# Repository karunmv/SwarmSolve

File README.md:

### Main
Entrypoint.

### esp_now_comms
Functions for inter-robot communications.

### feature_detection
Detects the current features of the maze.

Provides an interface to maneuver these features.

### motor_control
Drives the motors.

### QTRX-MD-NRC
Provides an interface for reading IR sensor values.

### utils
Utilitiy functions.

# TODO

Figure out watchdog thing

Convert num pulses to distance
Have exploration strategy be decided at runtime by which button gets pressed
Basic collision avoidance
generalize exploration algorithm

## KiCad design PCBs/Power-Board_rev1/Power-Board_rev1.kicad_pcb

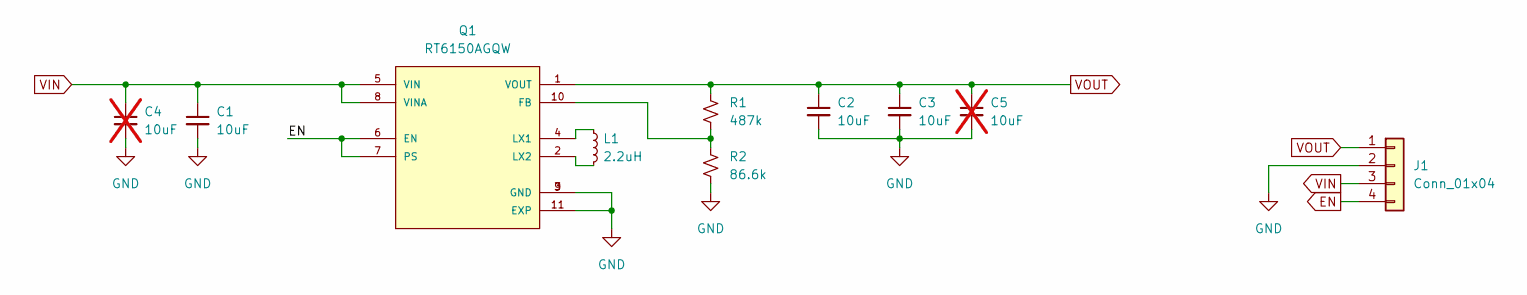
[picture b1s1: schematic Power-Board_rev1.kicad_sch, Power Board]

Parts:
C1, C2, C3: 10uF; C_0805_2012Metric_Pad1.18x1.45mm_HandSolder; JLCPCB Part# C95841
C4, C5: 10uF; C_0805_2012Metric_Pad1.18x1.45mm_HandSolder; JLCPCB Part# C95841; not fitted
J1: Conn_01x04; PinHeader_1x04_P2.54mm_Vertical_GND2
L1: 2.2uH; L_Changjiang_FTC252012S; JLCPCB Part# C5832372
Q1: RT6150AGQW; SON50P300X300X80-11N; JLCPCB Part# C147971
R1: 487k; R_0603_1608Metric_Pad0.98x0.95mm_HandSolder; JLCPCB Part# C23183
R2: 86.6k; R_0603_1608Metric_Pad0.98x0.95mm_HandSolder; JLCPCB Part# C23121

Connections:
/EN: J1.4, Q1.6 (EN), Q1.7 (PS)
/VIN: C1.1, C4.1, J1.3, Q1.5 (VIN), Q1.8 (VINA)
/VOUT: C2.1, C3.1, C5.1, J1.1, Q1.1 (VOUT), R1.1
GND: C1.2, C2.2, C3.2, C4.2, C5.2, J1.2, Q1.3 (GND), Q1.9 (GND), Q1.11 (EXP), R2.2
unnamed: Q1.10 (FB), R1.2, R2.1
unnamed: L1.1, Q1.4 (LX1)
unnamed: L1.2, Q1.2 (LX2)

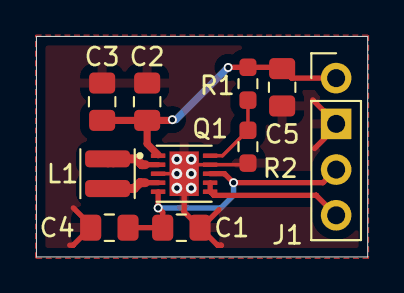
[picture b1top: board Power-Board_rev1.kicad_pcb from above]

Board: 4 copper layers, 18.4 x 12.2 mm, 10 parts (0 on the bottom side), 7 nets.

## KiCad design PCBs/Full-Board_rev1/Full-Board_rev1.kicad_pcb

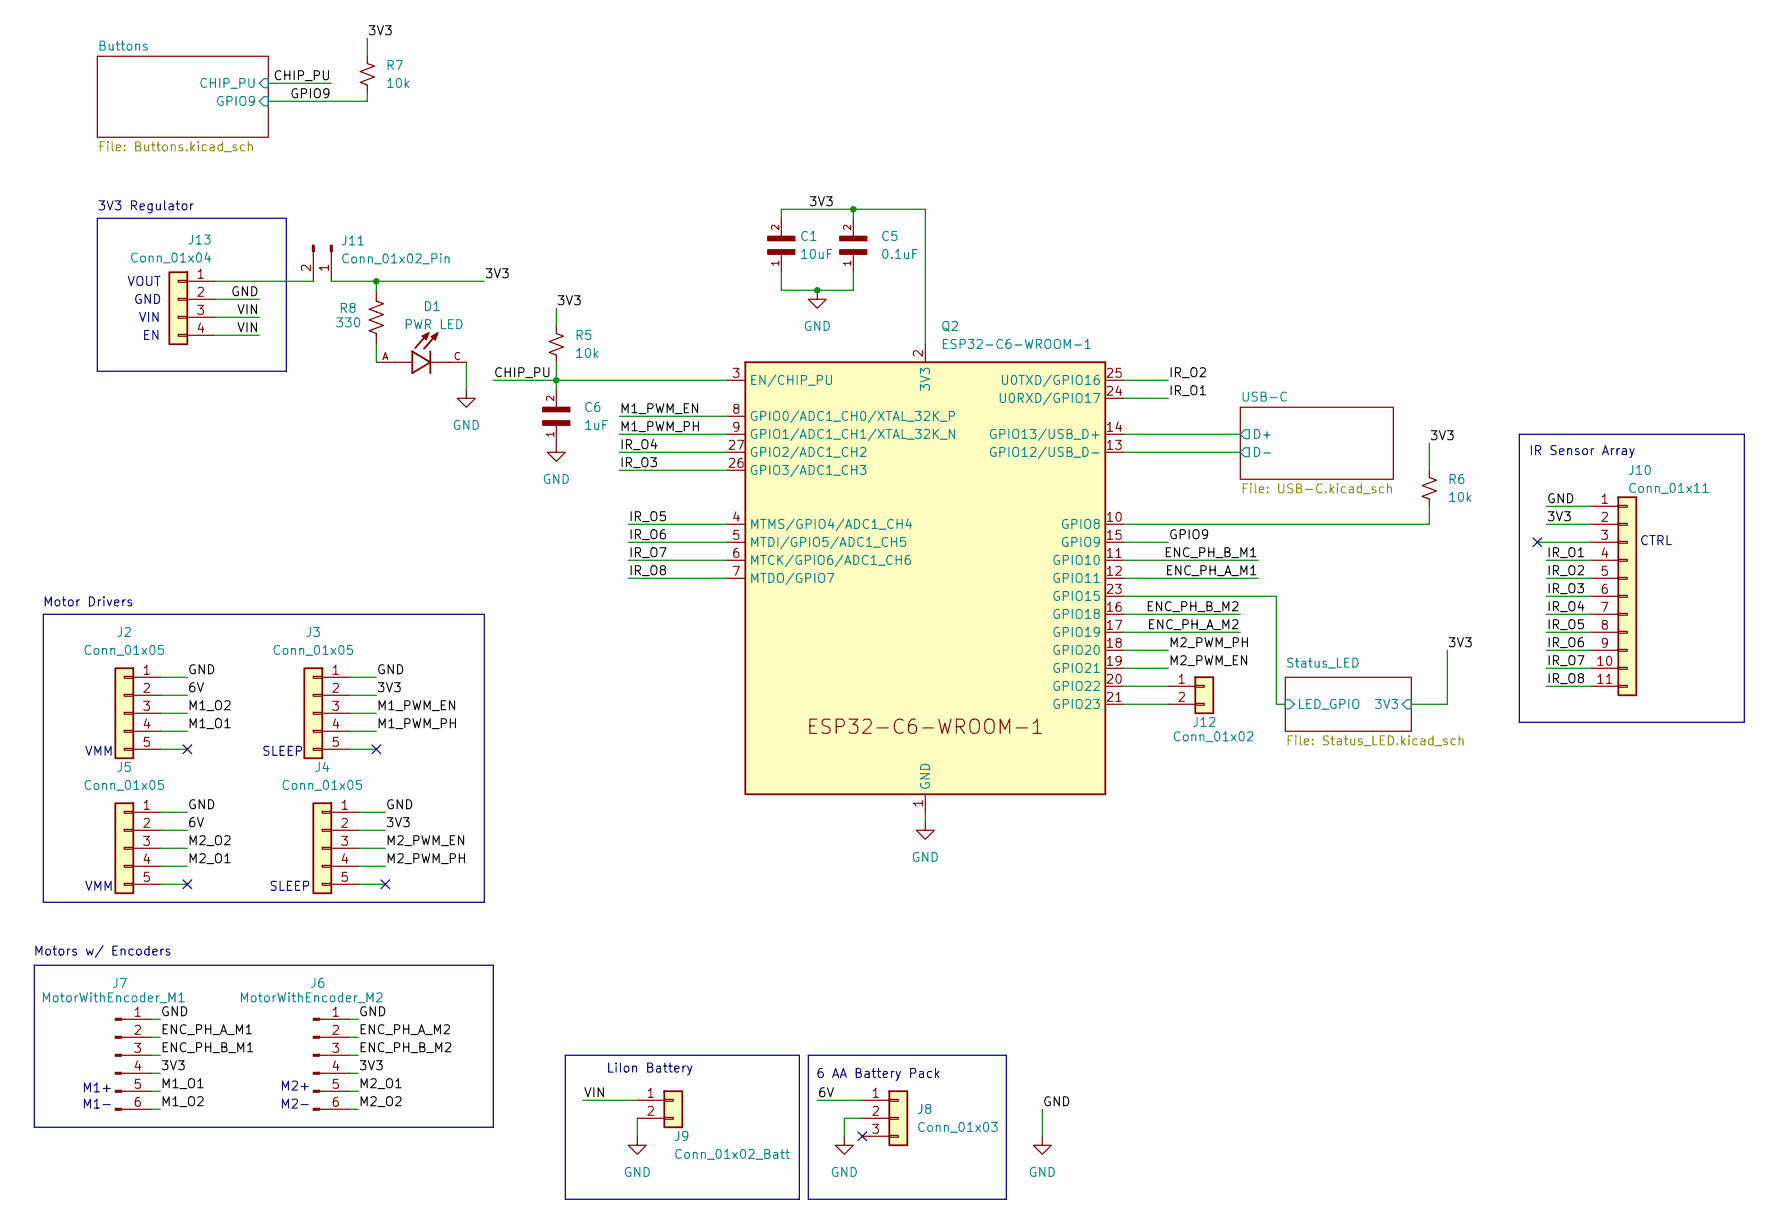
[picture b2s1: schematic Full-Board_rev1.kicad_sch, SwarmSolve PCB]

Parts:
C1: 10uF; C_0805_2012Metric_Pad1.18x1.45mm_HandSolder; PARTREV 20200310
C5: 0.1uF; C_0805_2012Metric_Pad1.18x1.45mm_HandSolder; PARTREV 20200310
C6: 1uF; C_0805_2012Metric_Pad1.18x1.45mm_HandSolder; PARTREV 20200310
D1: PWR LED; LED_KT-0603R; PARTREV 2013/01/24
J2, J3, J4, J5: Conn_01x05; PinSocket_1x05_P2.54mm_Vertical
J6: MotorWithEncoder_M2; PinSocket_1x06_P2.54mm_Vertical
J7: MotorWithEncoder_M1; PinSocket_1x06_P2.54mm_Vertical
J8: Conn_01x03; JST_PH_B3B-PH-K_1x03_P2.00mm_Vertical
J9: Conn_01x02_Batt; JST_PH_B2B-PH-K_1x02_P2.00mm_Vertical
J10: Conn_01x11; PinSocket_1x11_P2.54mm_Vertical
J11: Conn_01x02_Pin; PinHeader_1x02_P2.54mm_Vertical
J12: Conn_01x02; PinHeader_1x02_P2.54mm_Vertical
J13: Conn_01x04; PinSocket_1x04_P2.54mm_Vertical
Q2: ESP32-C6-WROOM-1
R5, R6, R7: 10k; R_Axial_DIN0207_L6.3mm_D2.5mm_P2.54mm_Vertical
R8: 330; R_Axial_DIN0207_L6.3mm_D2.5mm_P2.54mm_Vertical

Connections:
/3V3: C1.2, C5.2, J3.2, J4.2, J6.4, J7.4, J10.2, J11.1, Q2.2 (3V3), R5.1, R6.1, R7.1, R8.1; also elsewhere on the board
/6V: J2.2, J5.2, J8.1
/CHIP_PU: C6.2, Q2.3 (EN/CHIP_PU), R5.2; also elsewhere on the board
/ENC_PH_A_M1: J7.2, Q2.12 (GPIO11)
/ENC_PH_A_M2: J6.2, Q2.17 (GPIO19)
/ENC_PH_B_M1: J7.3, Q2.11 (GPIO10)
/ENC_PH_B_M2: J6.3, Q2.16 (GPIO18)
/GPIO9: Q2.15 (GPIO9), R7.2; also elsewhere on the board
/IR_O1: J10.4, Q2.24 (U0RXD/GPIO17)
/IR_O2: J10.5, Q2.25 (U0TXD/GPIO16)
/IR_O3: J10.6, Q2.26 (GPIO3/ADC1_CH3)
/IR_O4: J10.7, Q2.27 (GPIO2/ADC1_CH2)
/IR_O5: J10.8, Q2.4 (MTMS/GPIO4/ADC1_CH4)
/IR_O6: J10.9, Q2.5 (MTDI/GPIO5/ADC1_CH5)
/IR_O7: J10.10, Q2.6 (MTCK/GPIO6/ADC1_CH6)
/IR_O8: J10.11, Q2.7 (MTDO/GPIO7)
/M1_O1: J2.4, J7.5
/M1_O2: J2.3, J7.6
/M1_PWM_EN: J3.3, Q2.8 (GPIO0/ADC1_CH0/XTAL_32K_P)
/M1_PWM_PH: J3.4, Q2.9 (GPIO1/ADC1_CH1/XTAL_32K_N)
/M2_O1: J5.4, J6.5
/M2_O2: J5.3, J6.6
/M2_PWM_EN: J4.3, Q2.19 (GPIO21)
/M2_PWM_PH: J4.4, Q2.18 (GPIO20)
/Status_LED/LED_GPIO: Q2.23 (GPIO15); also elsewhere on the board
/USB-C/D+: Q2.14 (GPIO13/USB_D+); also elsewhere on the board
/USB-C/D-: Q2.13 (GPIO12/USB_D-); also elsewhere on the board
/VIN: J9.1, J13.3, J13.4
GND: C1.1, C5.1, C6.1, D1.C, J2.1, J3.1, J4.1, J5.1, J6.1, J7.1, J8.2, J9.2, J10.1, J13.2, Q2.1 (GND), Q2.28 (GND), Q2.29 (GND); also elsewhere on the board
unnamed: D1.A, R8.2
unnamed: J11.2, J13.1
unnamed: J12.1, Q2.20 (GPIO22)
unnamed: J12.2, Q2.21 (GPIO23)
unnamed: Q2.10 (GPIO8), R6.2

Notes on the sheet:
SLEEP
IR Sensor Array
M1+
6 AA Battery Pack
M2+
VOUT
GND
M2-
VIN
3V3 Regulator
VMM
LiIon Battery
Motors w/ Encoders
CTRL
M1-
Motor Drivers

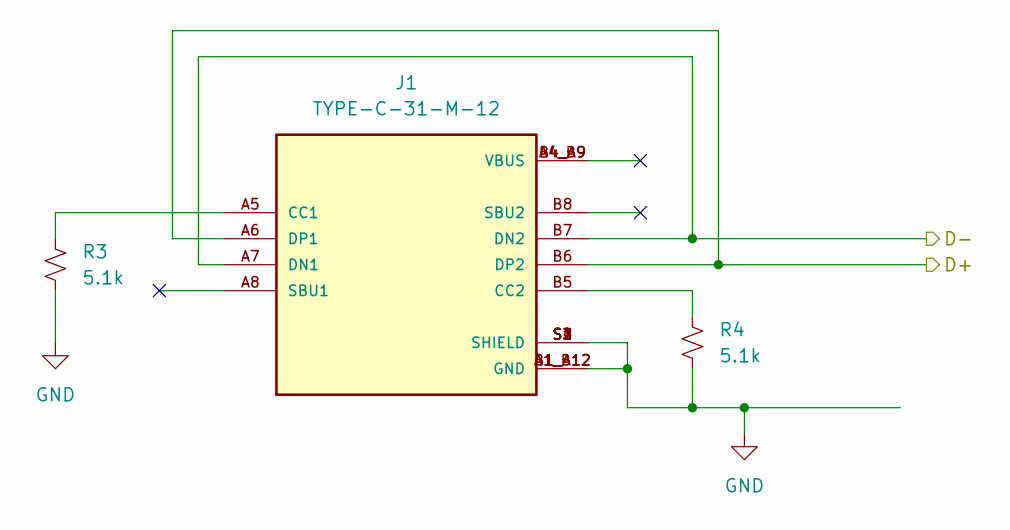
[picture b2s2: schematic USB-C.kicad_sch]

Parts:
J1: TYPE-C-31-M-12; HRO_TYPE-C-31-M-12; PARTREV 2020.12.08
R3, R4: 5.1k; R_Axial_DIN0207_L6.3mm_D2.5mm_P2.54mm_Vertical

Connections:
/USB-C/D+: J1.A6 (DP1), J1.B6 (DP2); also elsewhere on the board
/USB-C/D-: J1.A7 (DN1), J1.B7 (DN2); also elsewhere on the board
GND: J1.A1_B12 (GND), J1.B1_A12 (GND), J1.S1 (SHIELD), J1.S2 (SHIELD), J1.S3 (SHIELD), J1.S4 (SHIELD), R3.2, R4.2; also elsewhere on the board
unnamed: J1.A5 (CC1), R3.1
unnamed: J1.B5 (CC2), R4.1

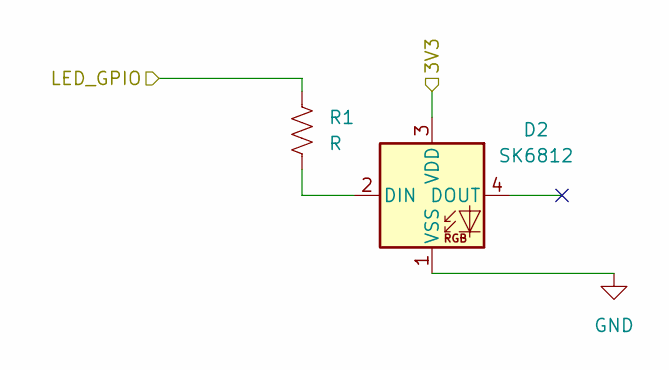
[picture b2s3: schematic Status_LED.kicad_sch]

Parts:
D2: SK6812; LED_SK6812_PLCC4_5.0x5.0mm_P3.2mm
R1: R; R_Axial_DIN0207_L6.3mm_D2.5mm_P2.54mm_Vertical

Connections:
/3V3: D2.3 (VDD); also elsewhere on the board
/Status_LED/LED_GPIO: R1.1; also elsewhere on the board
GND: D2.1 (VSS); also elsewhere on the board
unnamed: D2.2 (DIN), R1.2

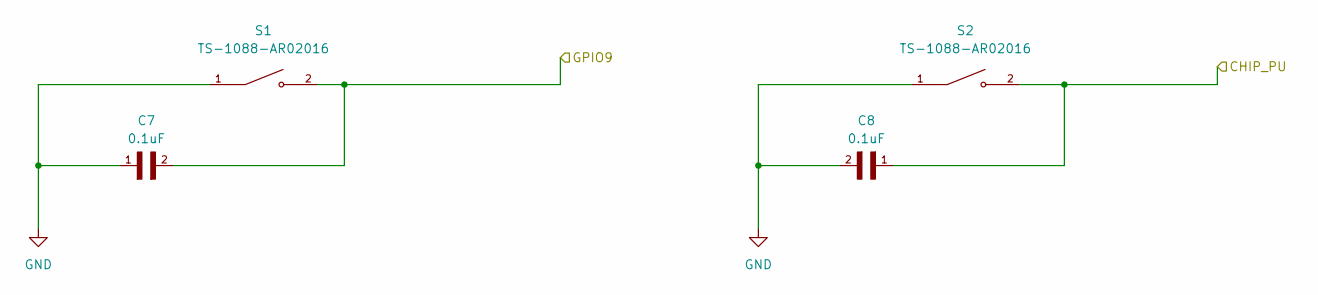
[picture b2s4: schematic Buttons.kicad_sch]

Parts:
C7, C8: 0.1uF; CAPRB500W50L400T250H550; PARTREV 20200310
S1, S2: TS-1088-AR02016; SW_TS-1088-AR02016; PARTREV N/A

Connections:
/CHIP_PU: C8.1, S2.2; also elsewhere on the board
/GPIO9: C7.2, S1.2; also elsewhere on the board
GND: C7.1, C8.2, S1.1, S2.1; also elsewhere on the board

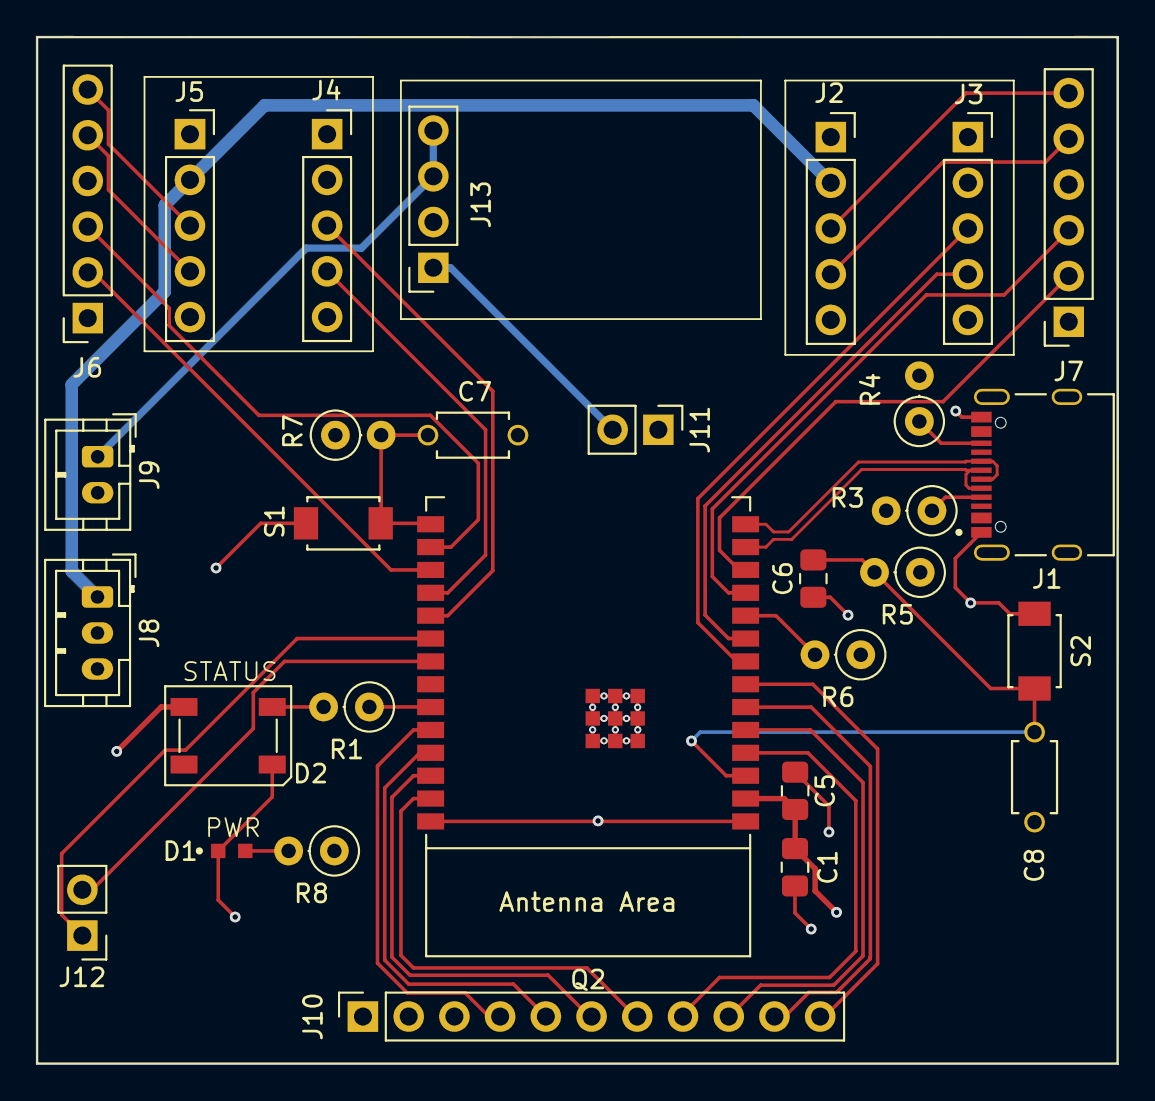
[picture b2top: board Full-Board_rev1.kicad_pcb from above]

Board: 4 copper layers, 60.1 x 57.1 mm, 30 parts (0 on the bottom side), 37 nets.

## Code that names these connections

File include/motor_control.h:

#ifndef MOTOR_CONTROL_H
#define MOTOR_CONTROL_H

#include "driver/ledc.h"


// GPIO Defines
#define M1_PWM 0
#define M1_DIR 1
#define M2_PWM 21
#define M2_DIR 20
#define ENC_PH_A_M1 11
#define ENC_PH_B_M1 10
#define ENC_PH_A_M2 19
#define ENC_PH_B_M2 18

// PWM Defines
#define LEDC_TIMER              LEDC_TIMER_0
#define LEDC_MODE               LEDC_LOW_SPEED_MODE
#define LEDC_CHANNEL            LEDC_CHANNEL_0
#define LEDC_DUTY_RES           LEDC_TIMER_13_BIT // Set duty resolution to 13 bits
#define LEDC_FREQUENCY          (4000) // Frequency in Hertz. Set frequency at 4 kHz

// Pulse Count Defines
#define PCNT_HIGH_LIMIT INT16_MAX
#define PCNT_LOW_LIMIT  INT16_MIN

/* Function Prototypes */

/**
 * @brief Initializes and returns a pulse counter that counts the pulses generated by the motor encoder
 * @param encoder_pins_A Pins for the A phase of the encoder
 * @param encoder_pins_B Pins for the B phase of the encoder
 */
pcnt_unit_handle_t init_encoder(uint32_t *encoder_pins_A, uint32_t *encoder_pins_B);

/**
 * @brief Initializes motor driver GPIO pins and pwm clocks
 * @param enable_pins Array of size NUM_MOTORS that holds the GPIO pins that are connected to the enable pins of the motor control board
 * @param enable_pins Array of size NUM_MOTORS that holds the GPIO pins that are connected to the phase pins of the motor control board
 */
void motor_setup(uint32_t *enable_pins, uint32_t *phase_pins);

/**
 * @brief Moves each motor individually at the speed provided (-100 -> 100) negative values are backwards
 * @param phase_pins Array of lengh NUM_MOTORS that defines the GPIO pins used for the phase (direction) of the motor
 * @param speeeds Array of length NUM_MOTORS that defines the speeds for each individual motor [LEFT MOTOR, RIGHT MOTOR]
 */
void move_motors(uint32_t *phase_pins, int8_t *speeds);

#endif

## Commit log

2025-08-22 arduino initial testing and prototyping
2025-08-25 added initial KiCad project files
2025-08-25 cleaned PCB branch
2025-08-25 cleaned main branch
2025-08-25 DC-DC base schematic created
2025-08-26 added modular design
2025-08-27 buttons and esp32 added
2025-08-27 Added USB-C
2025-08-27 added ESP32 peripherals
2025-08-28 LEDs added
2025-08-28 Motor driver, motor+encoder headers added
2025-09-02 Adjusted and Added headers to schematic
2025-09-02 Added current measurement jumper
2025-09-02 Fixed some rules checker errors
2025-09-02 Added Espressif library
2025-09-02 Added Espressif library (for real)
2025-09-03 created new power board project
2025-09-04 Power board schematic done
2025-09-04 Added footprints for main board components
2025-09-04 Added new part libs
2025-09-05 Changed capacitor footprints and added libs of same
2025-09-05 Redid some faulty footprint assignments
2025-09-08 Power Board Schematic
2025-09-09 initial footprint layout + libs
2025-09-10 updated power board layout, added extra pads for additional capacitors
2025-09-11 Power board layout rev-1 mostly finished
2025-09-12 Added fabrication files for power board rev1
2025-09-12 Full Board PCB Design Rev1.0 complete
2025-09-12 Updated power board files
2025-09-12 Full Board PCB Design Rev1.1 complete
2025-09-12 Full Board v1 complete
2025-09-12 Full Board v1 complete frfr
2025-09-15 Made Power Board 4 Layers
2025-09-17 Added Panelized Board
2025-09-18 Created blank project
2025-09-24 basic project structure with communication receiving outline
2025-09-25 added sdkconfig defaults
2025-09-25 Added sender functions
2025-09-25 updated .gitignore, removed .vscode
2025-09-26 basic two way broadcast communication
2025-09-29 Started IR hardware driver
2025-09-30 IR sensor read function that prints raw values
2025-10-02 Tested on PCB, updated IR array data function to return values for all sensors in array
2025-10-15 base motor control code
2025-10-20 Motor PWM working
2025-10-21 fixed motor directions
2025-10-21 individual motor control
2025-10-22 Cleaned up code, added feature detection and utils files with basic structure
2025-10-22 updated feature detection and added outline for navigation
2025-10-23 minor modifications to feature detection
2025-10-23 added proportional control for line following
2025-10-23 Basic point of interest detection
2025-10-24 Better right turn navigation, better organization of feature detection, some u-turn functionality
2025-10-24 added calibration and played with error correction
2025-10-27 fixed line following threshold and adding debugging communication
2025-10-29 Improved line following error correction
2025-10-29 Added files
2025-10-30 organization of functions
2025-10-31 attempt to send ir values through esp-now
2025-10-31 added a difference term to follow line error; Needs testing
2025-11-03 Encoder initialization and functionality added to check straight
2025-11-04 PID Magic numbers found!
2025-11-05 Occupancy grid generation and pruning map initial code
    Occupancy grid, pruning
2025-11-05 Occupancy grid and map pruning (minor changes)
2025-11-06 Fixed PID error and adding centering function
2025-11-06 Added Left and U turns
2025-11-06 Some comments and cleanup
2025-11-11 Path list creation and path follow code
2025-11-11 Pruning v2
2025-11-11 updated path communication code
2025-11-11 updated pruning algorithm; added more manipulation functions; added final path generating function for secondary robot
2025-11-11 minor changes to pruning and path manipulation functions
2025-11-12 minor changes to main function (queue data stuff)
2025-11-12 pruning - works only for one u-turn
2025-11-12 Pruning and combining paths works
2025-11-13 Inter-robot path communication, pruning, and following working! Robots can now explore the maze and exit using the optimal path found by the other robot
2025-11-13 start of exploration with button press done
2025-11-17 Qualifiers
2025-11-20 Updated comments
2025-12-09 Switched from broadcast to peer-to-peer communication
2025-12-09 Doublechecks path when backtracking
2025-12-11 Added more comments
2025-12-11 Added left-right tuning parameter
2025-12-11 improved documentation and error handling
2025-12-15 Updated some comments and improved array bounds checking
2025-12-15 Added more comments; removed old code
2026-02-17 added some pin symbols
2026-02-17 restructured main layout, needs some cleanup still
2026-02-17 cleaned up schematic, everything is directly connected that can be, otherwise ports are used
2026-02-17 Updated comments and formatting
2026-02-17 make sure everything is saved and pushed
